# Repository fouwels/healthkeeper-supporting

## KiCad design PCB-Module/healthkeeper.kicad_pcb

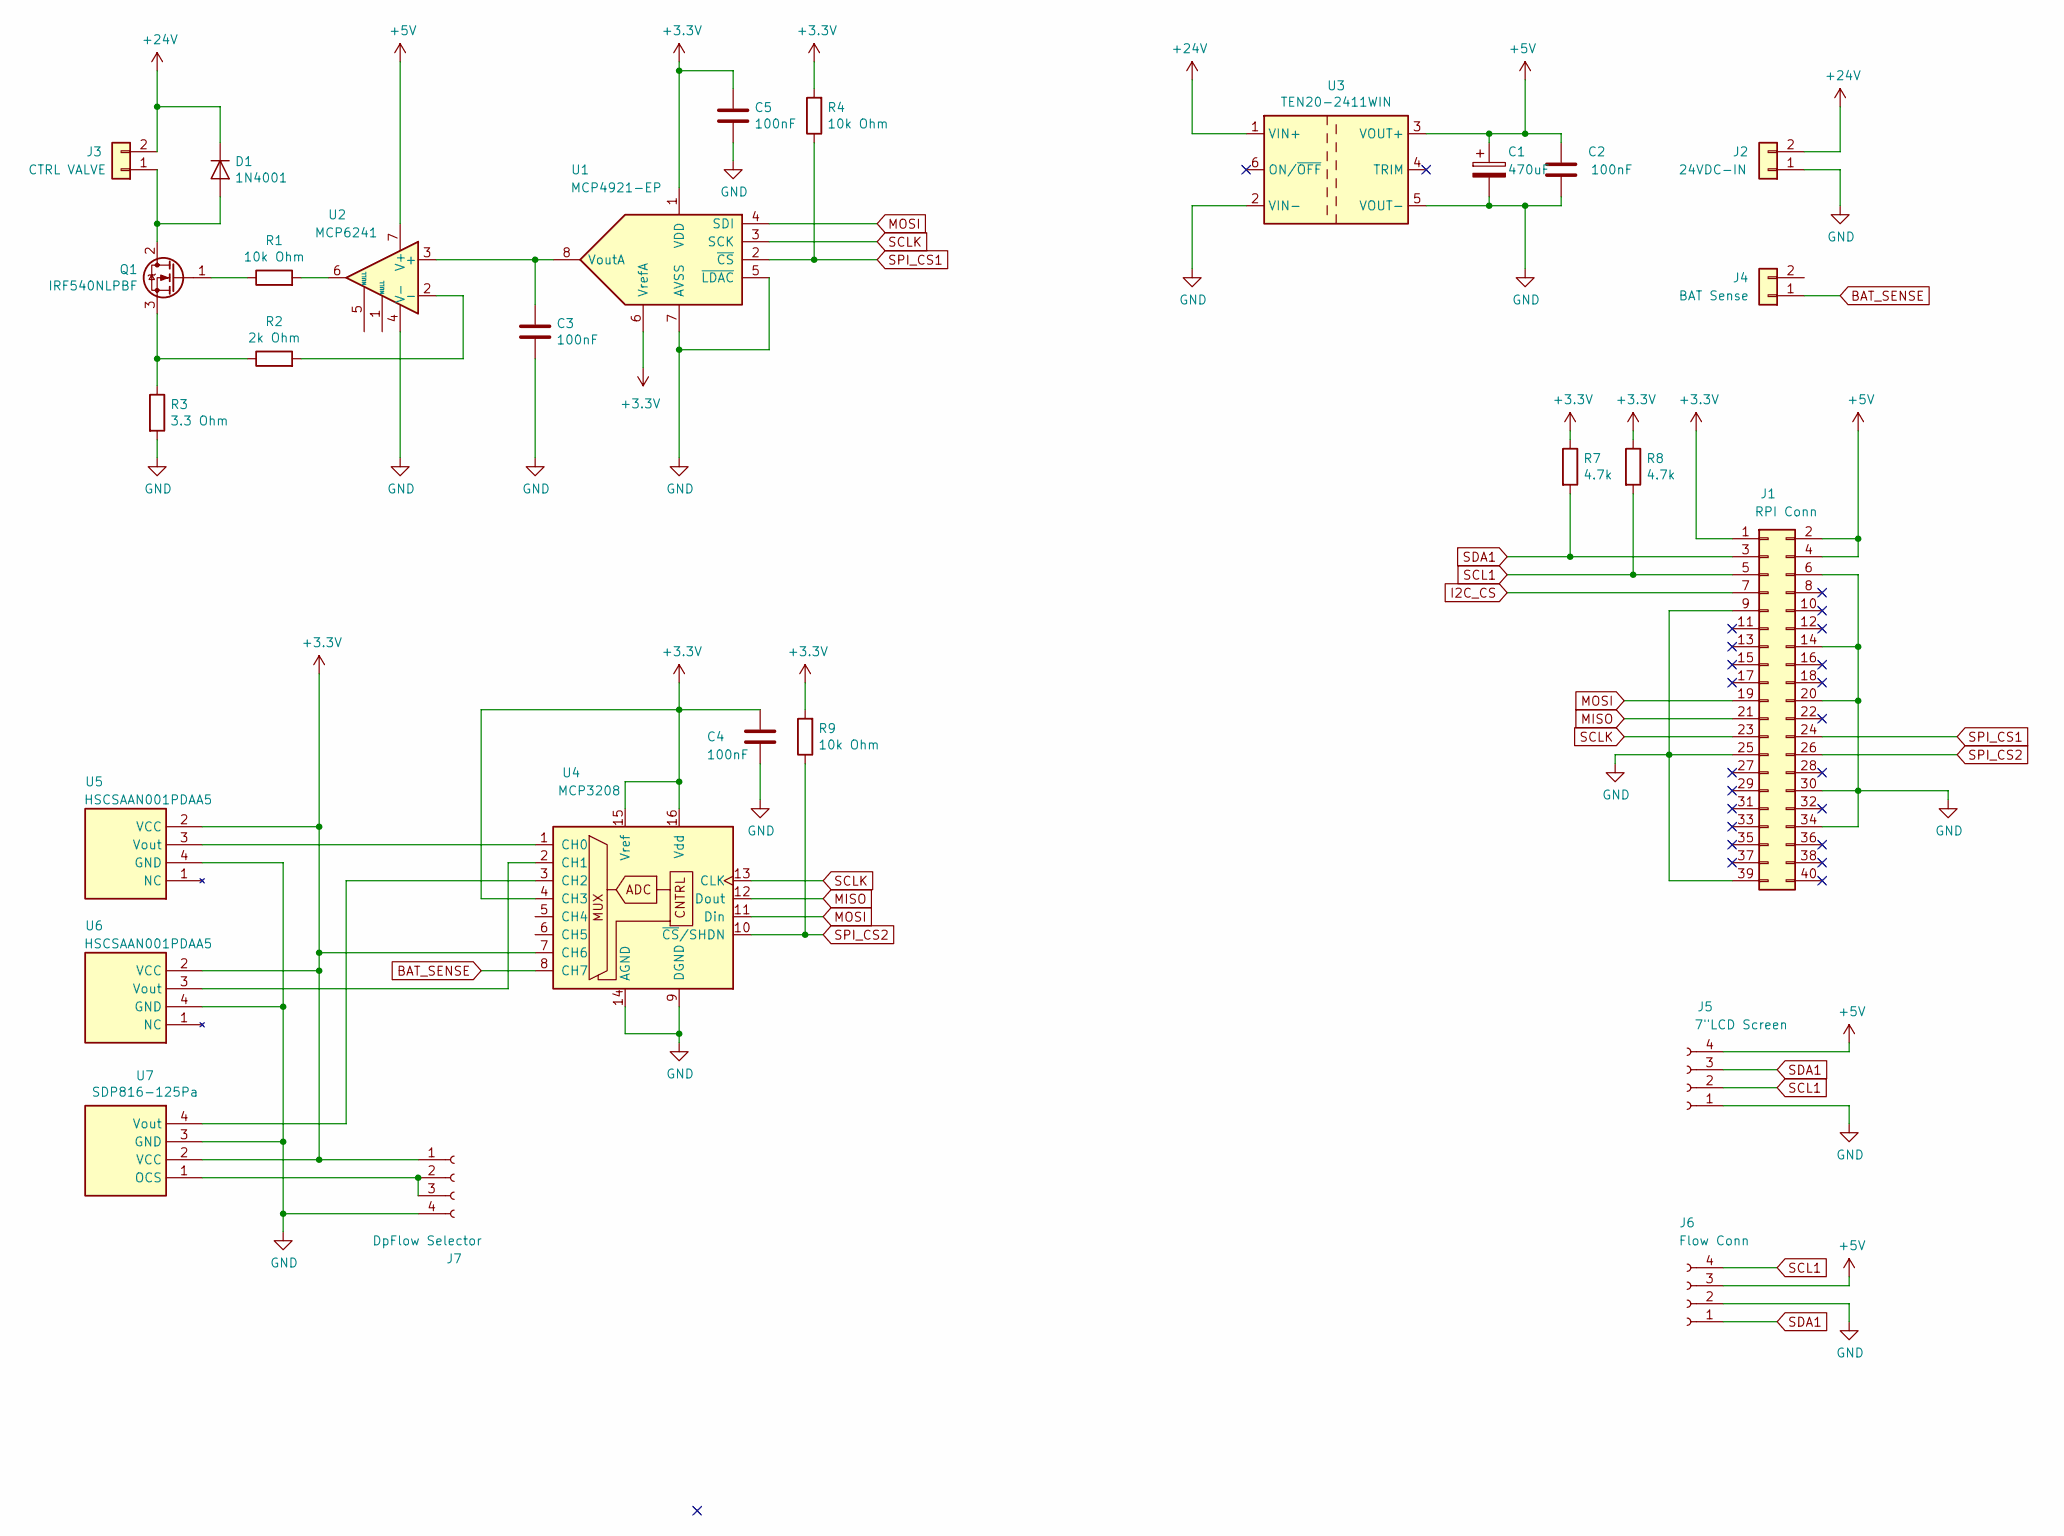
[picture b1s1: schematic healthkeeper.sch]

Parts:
C1: 470uF; CP_Radial_D10.0mm_P5.00mm
C2, C3, C4, C5: 100nF; C_Rect_L7.2mm_W2.5mm_P5.00mm_FKS2_FKP2_MKS2_MKP2
D1: 1N4001; D_DO-41_SOD81_P10.16mm_Horizontal
J1: RPI Conn; Raspberry_Pi4
J2: 24VDC-IN; Wago_734-132_1x02_P3.50mm_Vertical
J3: CTRL VALVE; Wago_734-132_1x02_P3.50mm_Vertical
J4: BAT Sense; Wago_734-132_1x02_P3.50mm_Vertical
J5: 7\"LCD Screen; PinHeader_1x04_P2.54mm_Vertical
J6: Flow Conn; PinHeader_1x04_P2.54mm_Vertical
J7: DpFlow Selector; PinHeader_1x04_P2.54mm_Vertical
Q1: IRF540NLPBF; TO-220-3_Vertical
R1, R4, R9: 10k Ohm; R_Axial_DIN0207_L6.3mm_D2.5mm_P10.16mm_Horizontal
R2: 2k Ohm; R_Axial_DIN0207_L6.3mm_D2.5mm_P10.16mm_Horizontal
R3: 3.3 Ohm; R_Axial_DIN0414_L11.9mm_D4.5mm_P20.32mm_Horizontal
R7, R8: 4.7k; R_Axial_DIN0207_L6.3mm_D2.5mm_P10.16mm_Horizontal
U1: MCP4921-EP; DIP-8_W7.62mm
U2: MCP6241; DIP-8_W7.62mm
U3: TEN20-2411WIN; THN15-2411WI
U4: MCP3208; DIP-16_W10.16mm
U5, U6: HSCSAAN001PDAA5; PinHeader_1x04_P2.54mm_Vertical
U7: SDP816-125Pa; SDP816125Pa

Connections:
+3V3: C4.1, C5.1, J1.1, J7.1, R4.2, R7.1, R8.1, R9.2, U1.1 (VDD), U1.6 (VrefA), U4.4 (CH3), U4.7 (CH6), U4.15 (Vref), U4.16 (Vdd), U5.2 (VCC), U6.2 (VCC), U7.2 (VCC)
+5V: C1.1, C2.2, J1.2, J1.4, J5.4, J6.3, U2.7 (V+), U3.3 (VOUT+)
+24V: D1.1 (K), J2.2, J3.2, U3.1 (VIN+)
BAT_SENSE: J4.1, U4.8 (CH7)
GND: C1.2, C2.1, C3.2, C4.2, C5.2, J1.6, J1.9, J1.14, J1.20, J1.25, J1.30, J1.34, J1.39, J2.1, J5.1, J6.2, J7.4, R3.2, U1.5 (~LDAC~), U1.7 (AVSS), U2.4 (V-), U3.2 (VIN-), U3.5 (VOUT-), U4.9 (DGND), U4.14 (AGND), U5.4 (GND), U6.4 (GND), U7.3 (GND)
I2C_CS: J1.7
MISO: J1.21, U4.12 (Dout)
MOSI: J1.19, U1.4 (SDI), U4.11 (Din)
unnamed: C3.1, U1.8 (VoutA), U2.3 (+)
unnamed: D1.2 (A), J3.1, Q1.2 (D)
unnamed: J7.2, J7.3, U7.1 (OCS)
unnamed: Q1.1 (G), R1.1
unnamed: Q1.3 (S), R2.1, R3.1
unnamed: R1.2, U2.6
unnamed: R2.2, U2.2 (-)
unnamed: U4.1 (CH0), U5.3 (Vout)
unnamed: U4.2 (CH1), U6.3 (Vout)
unnamed: U4.3 (CH2), U7.4 (Vout)
SCL1: J1.5, J5.2, J6.4, R8.2
SCLK: J1.23, U1.3 (SCK), U4.13 (CLK)
SDA1: J1.3, J5.3, J6.1, R7.2
SPI_CS1: J1.24, R4.1, U1.2 (~CS~)
SPI_CS2: J1.26, R9.1, U4.10 (~CS~/SHDN)

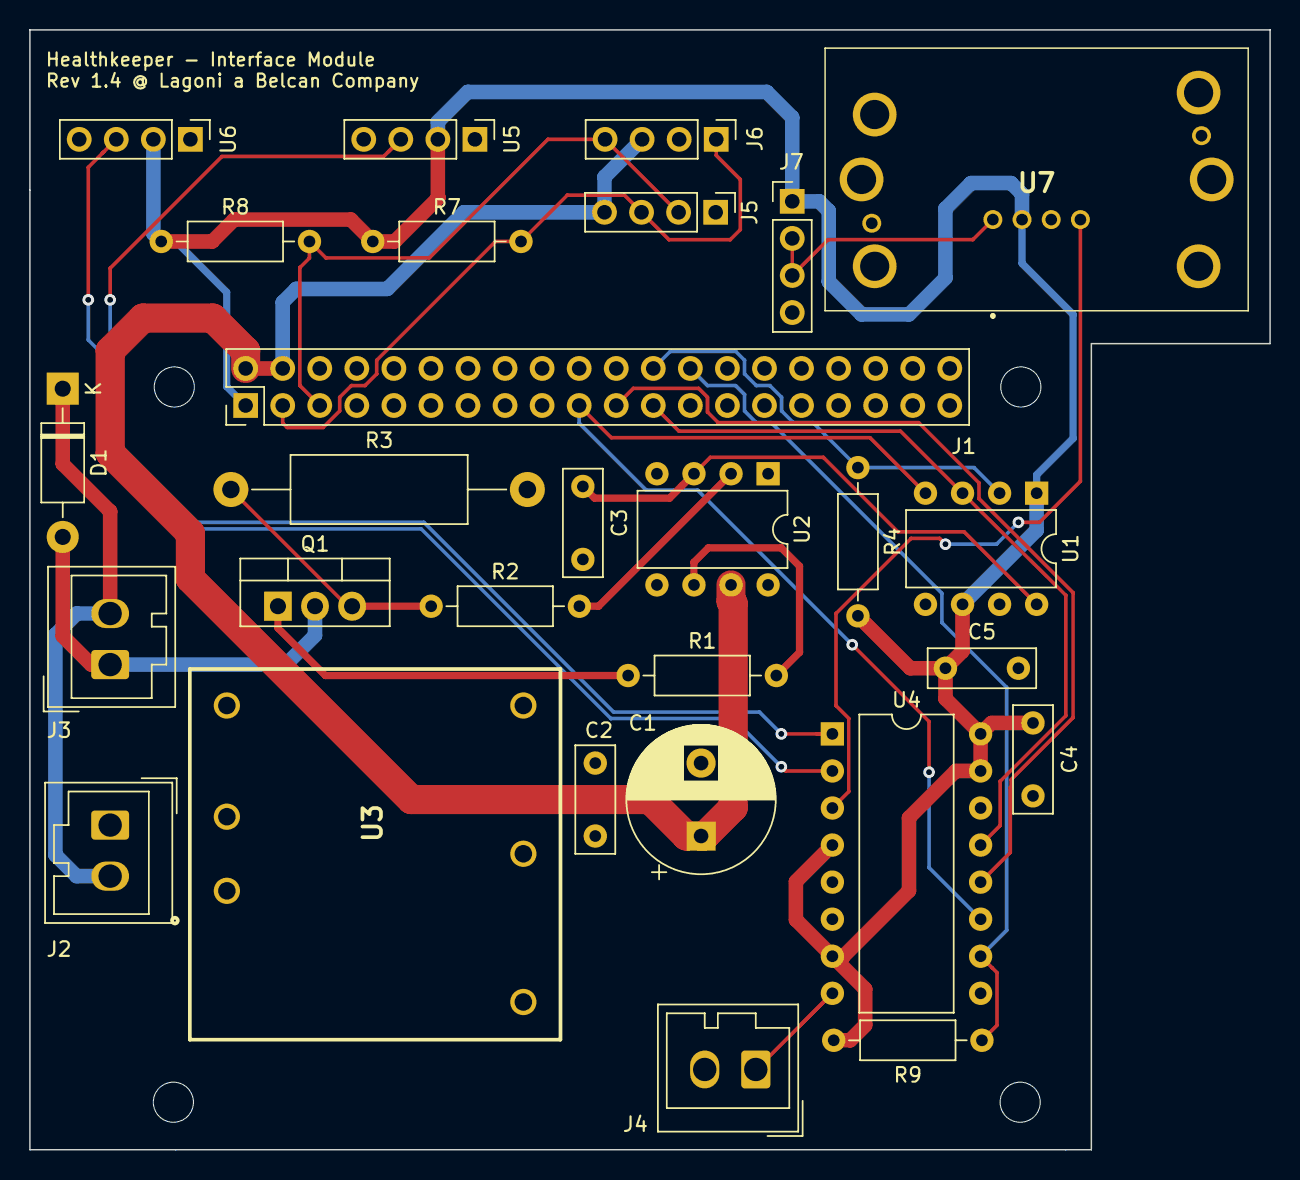
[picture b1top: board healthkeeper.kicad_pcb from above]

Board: 2 copper layers, 85.0 x 76.8 mm, 28 parts (0 on the bottom side), 22 nets.

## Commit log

2020-04-23 Schematic, PCB and 3D model added
    Added the schematic and PCB Rev 1.3
    3D model print files added
2020-04-23 Joint 24V and 5V ground
    Error in the Rev 1.3 design as the 24V and 5V power weren't connected. This leads to an issue with the valve control.
2020-04-23 Added the PCB footprint library
2020-04-23 Added RaspberryPI to the Footprint library
    Added RaspberryPI to the Footprint library
